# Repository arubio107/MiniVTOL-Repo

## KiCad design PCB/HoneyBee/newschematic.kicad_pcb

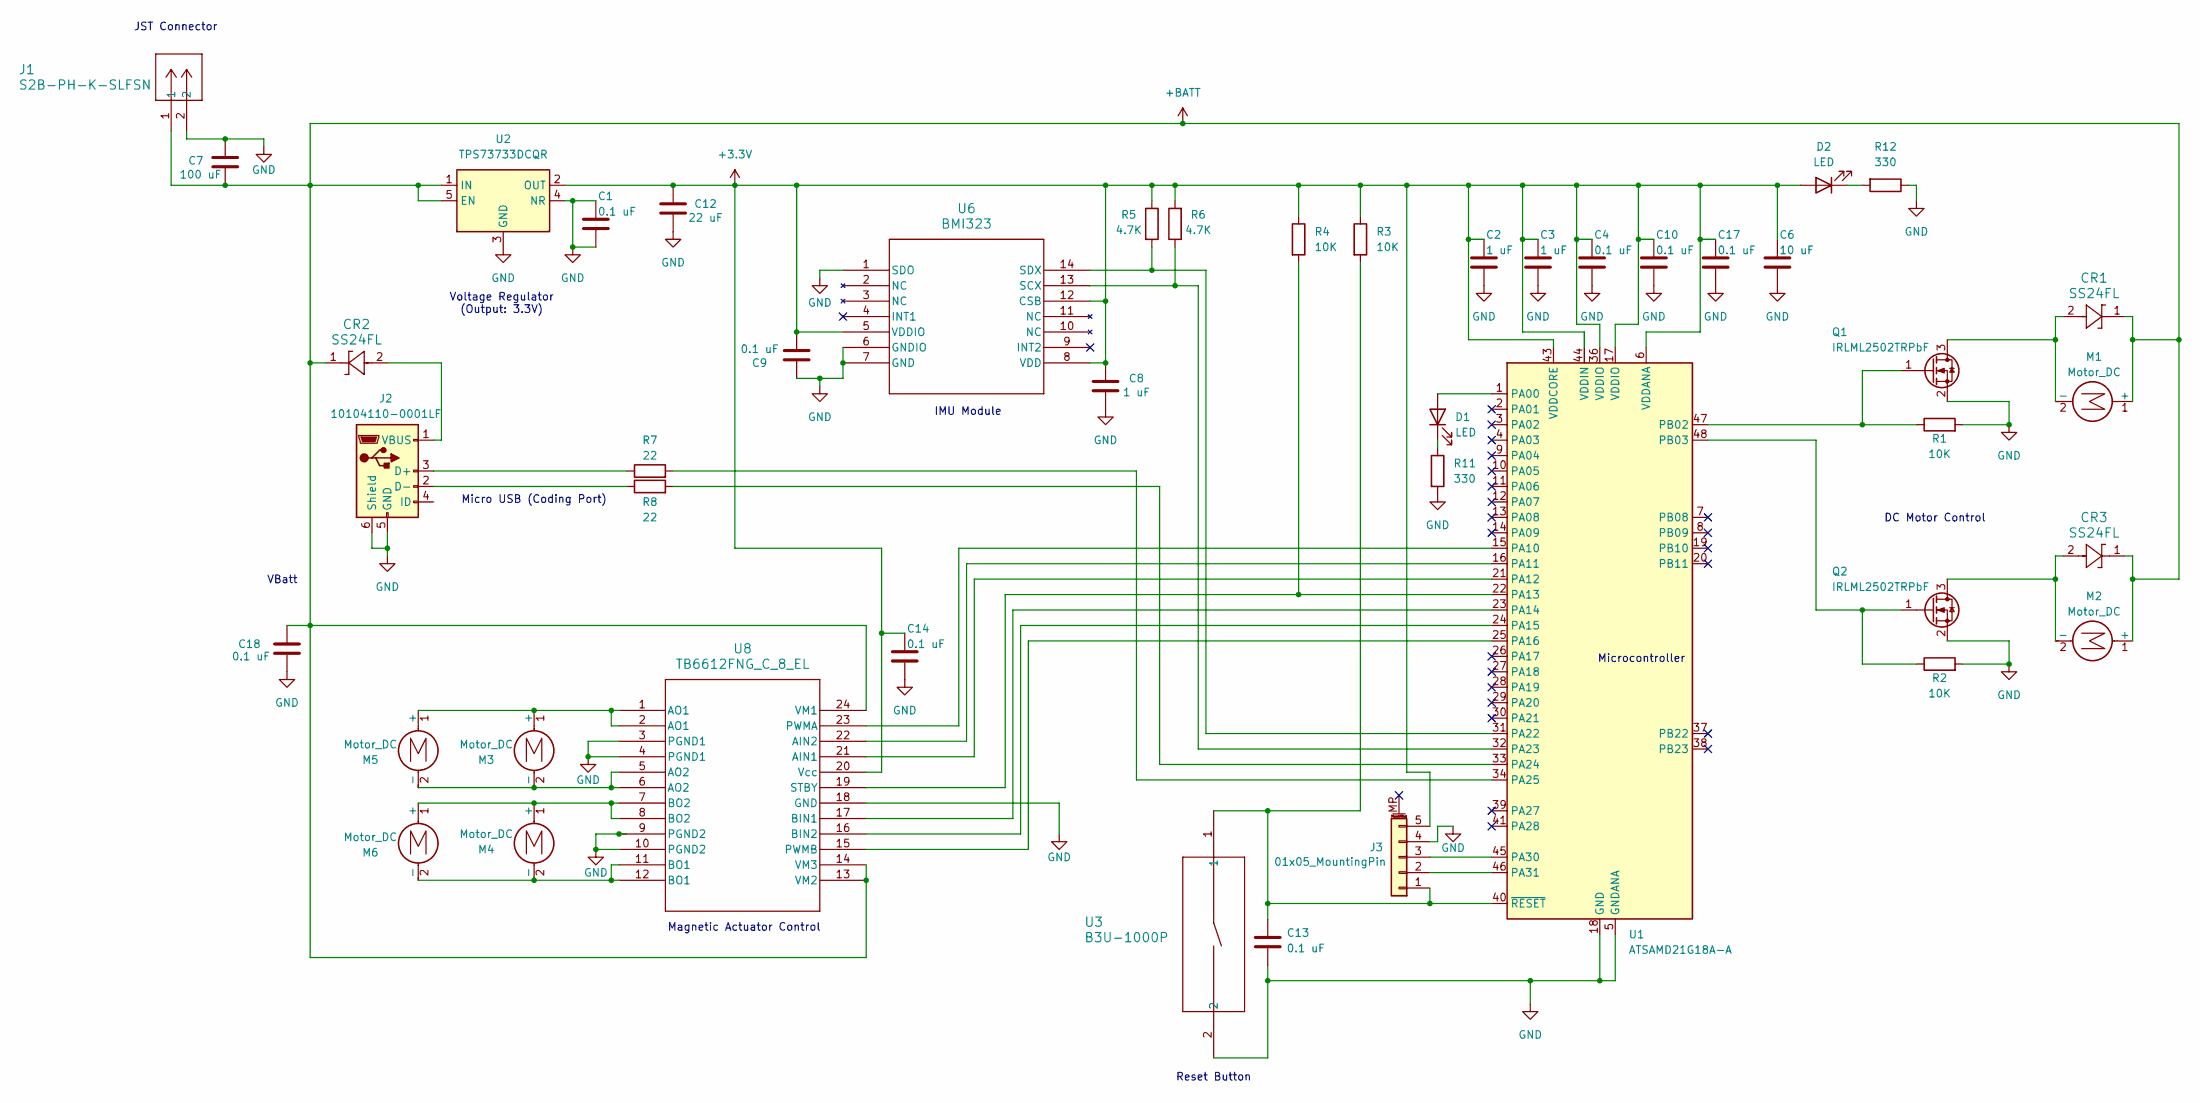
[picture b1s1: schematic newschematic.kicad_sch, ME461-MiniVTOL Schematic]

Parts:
C1, C4, C9, C10, C13, C14, C17, C18: 0.1 uF; C_0603_1608Metric_Pad1.08x0.95mm_HandSolder
C2, C3, C8: 1 uF; C_0603_1608Metric_Pad1.08x0.95mm_HandSolder
C6: 10 uF; C_0603_1608Metric_Pad1.08x0.95mm_HandSolder
C7: 100 uF; C_0805_2012Metric_Pad1.18x1.45mm_HandSolder
C12: 22 uF; C_0603_1608Metric_Pad1.08x0.95mm_HandSolder
CR1, CR2, CR3: SS24FL; D_SOD-123F
D1, D2: LED; LED_0603_1608Metric
J1: S2B-PH-K-SLFSN; JST_PH_S2B-PH-K_1x02_P2.00mm_Horizontal
J2: 10104110-0001LF; USB_Micro-B_Amphenol_10104110_Horizontal
J3: 01x05_MountingPin; PinHeader_1x05_P1.00mm_Vertical
M1, M2, M3, M4, M5, M6: Motor_DC; SolderWire-0.25sqmm_1x02_P4.2mm_D0.65mm_OD1.7mm
Q1, Q2: IRLML2502TRPbF; SOT-23W_Handsoldering
R1, R2, R3, R4: 10K; R_0603_1608Metric_Pad0.98x0.95mm_HandSolder
R5, R6: 4.7K; R_0603_1608Metric_Pad0.98x0.95mm_HandSolder
R7, R8: 22; R_0603_1608Metric_Pad0.98x0.95mm_HandSolder
R11, R12: 330; R_0603_1608Metric_Pad0.98x0.95mm_HandSolder
U1: ATSAMD21G18A-A; TQFP-48_7x7mm_P0.5mm
U2: TPS73733DCQR; SOT-223-6_TabPin3
U3: B3U-1000P; SW_SPST_B3U-1000P
U6: BMI323; Bosch_LGA-14_3x2.5mm_P0.5mm
U8: TB6612FNG_C_8_EL; SSOP-24_5.3x8.2mm_P0.65mm

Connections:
+3.3V: C2.1, C3.1, C4.1, C6.1, C8.1, C9.2, C10.1, C12.2, C14.1, C17.1, D2.2 (A), J3.5, R3.1, R4.1, R5.1, R6.2, U1.6 (VDDANA), U1.17 (VDDIO), U1.36 (VDDIO), U1.43 (VDDCORE), U1.44 (VDDIN), U2.2 (OUT), U6.5 (VDDIO), U6.8 (VDD), U6.12 (CSB), U8.20 (Vcc)
+BATT: C7.1, C18.1, CR1.1, CR2.1, CR3.1, J1.1, M1.1 (+), M2.1 (+), U2.1 (IN), U2.5 (EN), U8.13 (VM2), U8.14 (VM3), U8.24 (VM1)
GND: C1.1, C1.2, C2.2, C3.2, C4.2, C6.2, C7.2, C8.2, C9.1, C10.2, C12.1, C13.2, C14.2, C17.2, C18.2, J1.2, J2.5 (GND), J2.6 (Shield), J3.4, Q1.2 (S), Q2.2 (S), R1.2, R2.2, R11.2, R12.1, U1.5 (GNDANA), U1.18 (GND), U1.35 (GND), U1.42 (GND), U2.3 (GND), U2.4 (NR), U3.2, U6.1 (SDO), U6.6 (GNDIO), U6.7 (GND), U8.3 (PGND1), U8.4 (PGND1), U8.9 (PGND2), U8.10 (PGND2), U8.18 (GND)
unnamed: D1.2 (A), U1.1 (PA00)
unnamed: D1.1 (K), R11.1
unnamed: D2.1 (K), R12.2
unnamed: J2.3 (D+), R7.1
unnamed: J2.2 (D-), R8.1
unnamed: CR2.2, J2.1 (VBUS)
unnamed: C13.1, J3.1, R3.2, U1.40 (~RESET), U3.1
unnamed: J3.2, U1.46 (PA31)
unnamed: J3.3, U1.45 (PA30)
unnamed: CR1.2, M1.2 (-), Q1.3 (D)
unnamed: CR3.2, M2.2 (-), Q2.3 (D)
unnamed: M3.1 (+), M5.1 (+), U8.1 (AO1), U8.2 (AO1)
unnamed: M3.2 (-), M5.2 (-), U8.5 (AO2), U8.6 (AO2)
unnamed: M4.1 (+), M6.1 (+), U8.7 (BO2), U8.8 (BO2)
unnamed: M4.2 (-), M6.2 (-), U8.11 (BO1), U8.12 (BO1)
unnamed: Q1.1 (G), R1.1, U1.47 (PB02)
unnamed: Q2.1 (G), R2.1, U1.48 (PB03)
unnamed: U1.15 (PA10), U8.23 (PWMA)
unnamed: U1.16 (PA11), U8.22 (AIN2)
unnamed: U1.21 (PA12), U8.21 (AIN1)
unnamed: R4.2, U1.22 (PA13), U8.19 (STBY)
unnamed: U1.23 (PA14), U8.17 (BIN1)
unnamed: U1.24 (PA15), U8.16 (BIN2)
unnamed: U1.25 (PA16), U8.15 (PWMB)
unnamed: R5.2, U1.31 (PA22), U6.14 (SDX)
unnamed: R6.1, U1.32 (PA23), U6.13 (SCX)
unnamed: R8.2, U1.33 (PA24)
unnamed: R7.2, U1.34 (PA25)

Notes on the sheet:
IMU Module
Reset Button
Micro USB (Coding Port)
DC Motor Control
Microcontroller
Magnetic Actuator Control
Voltage Regulator (Output: 3.3V)
VBatt
JST Connector

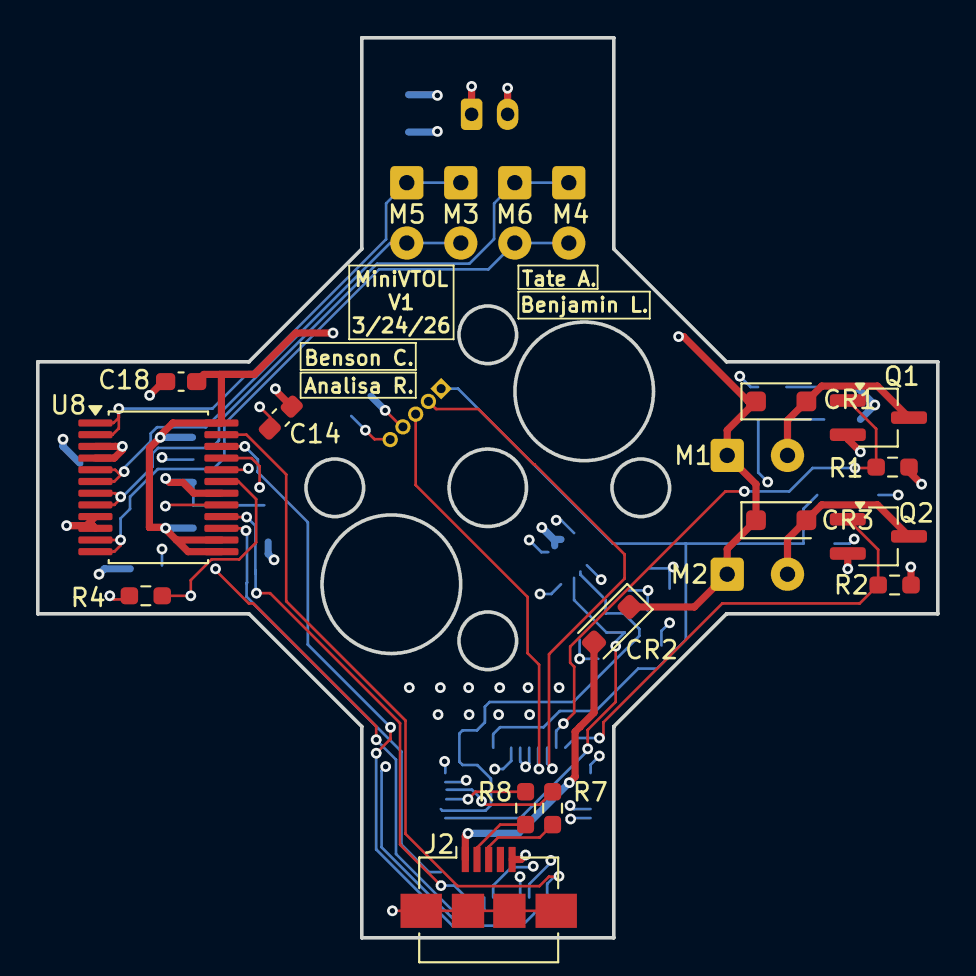
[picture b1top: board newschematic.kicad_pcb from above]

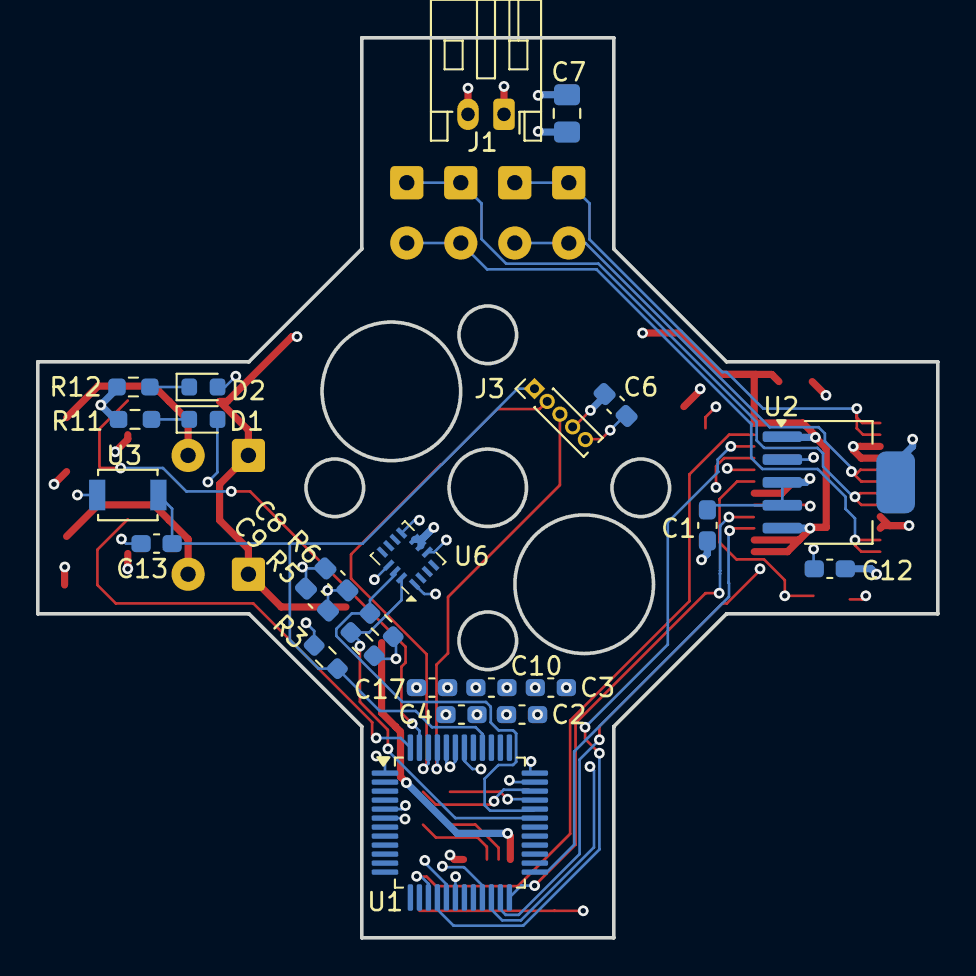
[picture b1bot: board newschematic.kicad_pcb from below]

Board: 4 copper layers, 50.0 x 50.0 mm, 45 parts (25 on the bottom side), 31 nets.

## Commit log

2025-11-13 Create KiCAD
2025-11-18 B's Schematic V1
    Wiring schematic, no PCB design yet
2026-02-01 PCB Schematic (2/1/26)
    No reset button or battery capacity monitor (voltage divider)
2026-02-01 PCB Schematic (2/1/26)
    No reset button, No voltage divider for battery capacity monitoring
2026-02-02 Add files via upload
    4 actuators
2026-02-05 Create Symbols and Footprints
2026-02-19 Cleaned up Repo
2026-02-19 Small updates
2026-02-19 PDF of Schematic Added
2026-02-24 Updated BOM, Changed Components
    Added "Price" and "DigiKey" to BOM
    Changed out of stock components and non-Cut Reel components.
2026-02-24 Small Tweaks
2026-02-25 BOM Updates
2026-03-19 PCB Draft 1-Minimal Wiring
    Still adjusting location of components.
2026-03-24 PCB Design V1
2026-03-24 PCB Design and Schematic V1
2026-03-25 PCB Design V2
    Added GND pads back to micro usb, fixed wiring
2026-03-25 Final touches
2026-03-25 Added power and signal LEDs, Added text
2026-03-25 Final Design + Gerber Files
2026-03-25 Updated Gerber FIles
2026-03-25 PCB Photos
2026-04-16 Removed regulator resistors, Added capacitor
